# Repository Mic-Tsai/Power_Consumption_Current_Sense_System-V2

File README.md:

## Power Consumption | Current Sense System V2

Arduino based power consumption calculator. Print results as UART interface and OLED display, also have SD card to log data.

Maximum 8 differential channels, come out with 4x ADS1115 in one I2C bus. RGB OLED display (ST7789 130x160) results show as a real-time update also supports the SD card data log. 

** **Important** **

Before you log the power consumption results, the resistor value needs to be calculated by the multimeter. You can press the button to do the value change very quickly! 

After the data logging into the SD card, plot data into an image via a python script.
## 

Any question or need technical support:

* Contact me via mail (xbcke12345@gmail.com)
* If this project helping. Please generously support =)

##

## 

>### License Information
>>This product is open source! Both, our hardware and software are open source and licensed under the following:
>>#### Hardware
>>>All hardware is released under [Creative Commons Share-alike 4.0 International](http://creativecommons.org/licenses/by-sa/4.0/).
>>#### Software 
>>>All software is released under the MIT License [http://opensource.org/licenses/MIT](http://opensource.org/licenses/MIT).
>>#### Documentation
>>>The documentation on this page is released under [Creative Commons Share-alike 4.0 International](http://creativecommons.org/licenses/by-sa/4.0/).

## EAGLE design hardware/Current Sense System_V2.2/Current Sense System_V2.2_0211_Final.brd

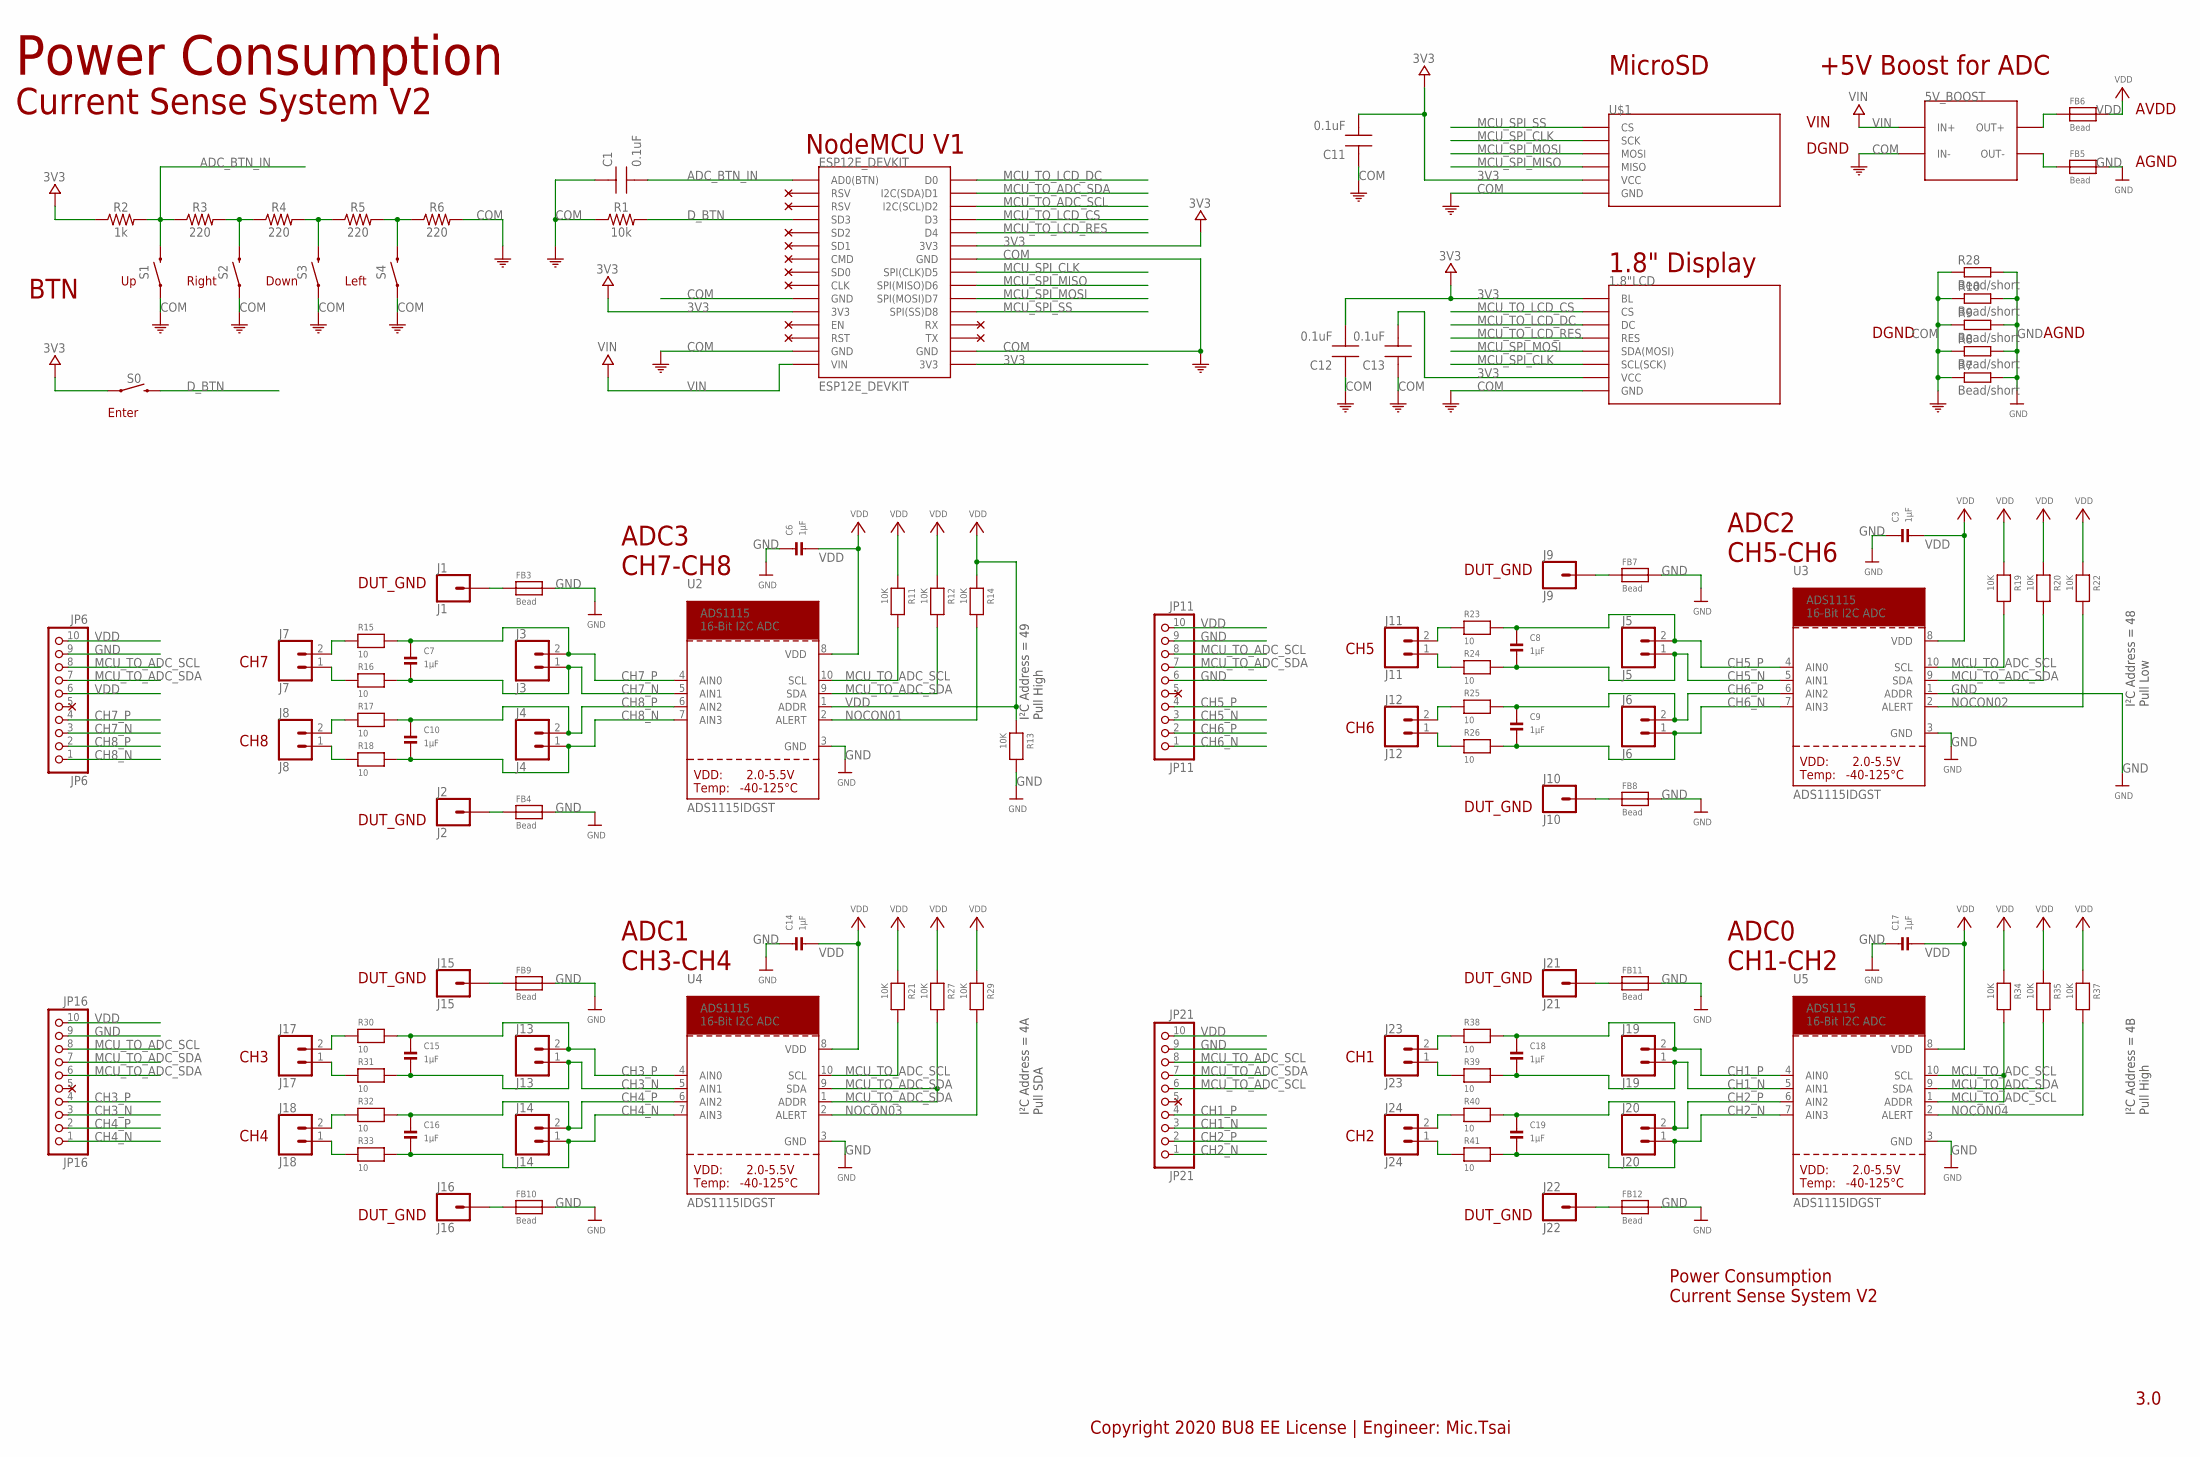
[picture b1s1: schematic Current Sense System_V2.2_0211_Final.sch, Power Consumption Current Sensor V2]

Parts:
1.8"LCD: 1.8"LCD"; 1.8"LCD
5V_BOOST: 5VBOOST"; 5VBOOST
C1, C11, C12, C13: 0.1uF; CAP0805-NP
C3, C6, C7, C8, C9, C10, C14, C15, C16, C17, C18, C19: 1µF; 0805
ESP12E_DEVKIT: ESP12E_DEVKIT
FB3, FB4, FB5, FB6, FB7, FB8, FB9, FB10, FB11, FB12: Bead; 0805
J1: J1; 1X01
J2: J2; 1X01
J3: J3; 1X02
J4: J4; 1X02
J5: J5; 1X02
J6: J6; 1X02
J7: J7; 1X02
J8: J8; 1X02
J9: J9; 1X01
J10: J10; 1X01
J11: J11; 1X02
J12: J12; 1X02
J13: J13; 1X02
J14: J14; 1X02
J15: J15; 1X01
J16: J16; 1X01
J17: J17; 1X02
J18: J18; 1X02
J19: J19; 1X02
J20: J20; 1X02
J21: J21; 1X01
J22: J22; 1X01
J23: J23; 1X02
J24: J24; 1X02
JP6: JP6; 1X10_ROUND70
JP11: JP11; 1X10_ROUND70
JP16: JP16; 1X10_ROUND70
JP21: JP21; 1X10_ROUND70
R1: 10k; 0805
R2: 1k; 0805
R3, R4, R5, R6: 220; 0805
R7, R8, R9, R10, R28: Bead/short; R0603
R11, R12, R13, R14, R19, R20, R21, R22, R27, R29, R34, R35, R37: 10K; 0805
R15, R16, R17, R18, R23, R24, R25, R26, R30, R31, R32, R33, R38, R39, R40, R41: 10; 0805
S0, S1, S2, S3, S4: MOMENTARY-SWITCH-SPST-PTH-6.0MM; TACTILE_SWITCH_PTH_6.0MM
U2, U3, U4, U5: ADS1115IDGST; MSOP10
U$1: MICROSD"; MICROSD

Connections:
3V3: 1.8"LCD.BL, 1.8"LCD.VCC(3V3) (VCC), C11.2, C12.2, C13.2, ESP12E_DEVKIT.3V3@0 (3V3), ESP12E_DEVKIT.3V3@1 (3V3), ESP12E_DEVKIT.3V3@2 (3V3), R2.1, S0.1, U$1.VCC(5V) (VCC)
ADC_BTN_IN: C1.2, ESP12E_DEVKIT.AD0 (AD0(BTN)), R2.2, R3.1, S1.3 (2)
CH1_N: C18.2, J19.1, JP21.3, R39.2, U5.5 (AIN1)
CH1_P: C18.1, J19.2, JP21.4, R38.2, U5.4 (AIN0)
CH2_N: C19.2, J20.1, JP21.1, R41.2, U5.7 (AIN3)
CH2_P: C19.1, J20.2, JP21.2, R40.2, U5.6 (AIN2)
CH3_N: C15.2, J13.1, JP16.3, R31.2, U4.5 (AIN1)
CH3_P: C15.1, J13.2, JP16.4, R30.2, U4.4 (AIN0)
CH4_N: C16.2, J14.1, JP16.1, R33.2, U4.7 (AIN3)
CH4_P: C16.1, J14.2, JP16.2, R32.2, U4.6 (AIN2)
CH5_N: C8.2, J5.1, JP11.3, R24.2, U3.5 (AIN1)
CH5_P: C8.1, J5.2, JP11.4, R23.2, U3.4 (AIN0)
CH6_N: C9.2, J6.1, JP11.1, R26.2, U3.7 (AIN3)
CH6_P: C9.1, J6.2, JP11.2, R25.2, U3.6 (AIN2)
CH7_N: C7.2, J3.1, JP6.3, R16.2, U2.5 (AIN1)
CH7_P: C7.1, J3.2, JP6.4, R15.2, U2.4 (AIN0)
CH8_N: C10.2, J4.1, JP6.1, R18.2, U2.7 (AIN3)
CH8_P: C10.1, J4.2, JP6.2, R17.2, U2.6 (AIN2)
COM: 1.8"LCD.GND, 5V_BOOST.IN-, C1.1, C11.1, C12.1, C13.1, ESP12E_DEVKIT.GND@0 (GND), ESP12E_DEVKIT.GND@1 (GND), ESP12E_DEVKIT.GND@2 (GND), ESP12E_DEVKIT.GND@3 (GND), R1.1, R6.2, R7.1, R8.1, R9.1, R10.1, R28.1, S1.1, S2.1, S3.1, S4.1, U$1.GND
D_BTN: ESP12E_DEVKIT.SD3, R1.2, S0.3 (2)
GND: C3.1, C6.1, C14.1, C17.1, FB3.2, FB4.2, FB5.2, FB7.2, FB8.2, FB9.2, FB10.2, FB11.2, FB12.2, JP6.9, JP11.6, JP11.9, JP16.9, JP21.9, R7.2, R8.2, R9.2, R10.2, R13.2, R28.2, U2.3 (GND), U3.1 (ADDR), U3.3 (GND), U4.3 (GND), U5.3 (GND)
MCU_SPI_CLK: 1.8"LCD.SCL(SCK), ESP12E_DEVKIT.D5 (SPI(CLK)D5), U$1.SCK
MCU_SPI_MISO: ESP12E_DEVKIT.D6 (SPI(MISO)D6), U$1.MISO
MCU_SPI_MOSI: 1.8"LCD.SDA(MOSI), ESP12E_DEVKIT.D7 (SPI(MOSI)D7), U$1.MOSI
MCU_SPI_SS: ESP12E_DEVKIT.D8 (SPI(SS)D8), U$1.CS
MCU_TO_ADC_SCL: ESP12E_DEVKIT.D2 (I2C(SCL)D2), JP6.8, JP11.8, JP16.8, JP21.6, JP21.8, R11.2, R19.2, R21.2, R34.2, U2.10 (SCL), U3.10 (SCL), U4.10 (SCL), U5.1 (ADDR), U5.10 (SCL)
MCU_TO_ADC_SDA: ESP12E_DEVKIT.D1 (I2C(SDA)D1), JP6.7, JP11.7, JP16.6, JP16.7, JP21.7, R12.2, R20.2, R27.2, R35.2, U2.9 (SDA), U3.9 (SDA), U4.1 (ADDR), U4.9 (SDA), U5.9 (SDA)
MCU_TO_LCD_CS: 1.8"LCD.CS, ESP12E_DEVKIT.D3
MCU_TO_LCD_DC: 1.8"LCD.DC, ESP12E_DEVKIT.D0
MCU_TO_LCD_RES: 1.8"LCD.RES, ESP12E_DEVKIT.D4
unnamed: FB3.1, J1.1
unnamed: FB4.1, J2.1
unnamed: J7.2, R15.1
unnamed: J7.1, R16.1
unnamed: J8.2, R17.1
unnamed: J8.1, R18.1
unnamed: 5V_BOOST.OUT-, FB5.1
unnamed: 5V_BOOST.OUT+, FB6.1
unnamed: FB7.1, J9.1
unnamed: FB8.1, J10.1
unnamed: J11.2, R23.1
unnamed: J11.1, R24.1
unnamed: J12.2, R25.1
unnamed: J12.1, R26.1
unnamed: FB9.1, J15.1
unnamed: R3.2, R4.1, S2.3 (2)
unnamed: R4.2, R5.1, S3.3 (2)
unnamed: R5.2, R6.1, S4.3 (2)
unnamed: FB10.1, J16.1
unnamed: J17.2, R30.1
unnamed: J17.1, R31.1
unnamed: J18.2, R32.1
unnamed: J18.1, R33.1
unnamed: FB11.1, J21.1
unnamed: FB12.1, J22.1
unnamed: J23.2, R38.1
unnamed: J23.1, R39.1
unnamed: J24.2, R40.1
unnamed: J24.1, R41.1
NOCON01: R14.2, U2.2 (ALERT)
NOCON02: R22.2, U3.2 (ALERT)
NOCON03: R29.2, U4.2 (ALERT)
NOCON04: R37.2, U5.2 (ALERT)
VDD: C3.2, C6.2, C14.2, C17.2, FB6.2, JP6.6, JP6.10, JP11.10, JP16.10, JP21.10, R11.1, R12.1, R13.1, R14.1, R19.1, R20.1, R21.1, R22.1, R27.1, R29.1, R34.1, R35.1, R37.1, U2.1 (ADDR), U2.8 (VDD), U3.8 (VDD), U4.8 (VDD), U5.8 (VDD)
VIN: 5V_BOOST.IN+, ESP12E_DEVKIT.VIN

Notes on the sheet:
Power Consumption
3.0
NodeMCU V1
+5V Boost for ADC
Power Consumption Current Sense System V2
Current Sense System V2
BTN
Right
Down
Left
Enter
1.8" Display
MicroSD
I²C Address = 49 Pull High
ADC3 CH7-CH8
ADS1115 16-Bit I2C ADC
CH7
CH8
DUT_GND
I²C Address = 48 Pull Low
ADC2 CH5-CH6
CH5
CH6
I²C Address = 4A Pull SDA
ADC1 CH3-CH4
CH3
CH4
I²C Address = 4B Pull High
ADC0 CH1-CH2
CH1
CH2
AVDD
AGND
VIN
DGND
Copyright 2020 BU8 EE License | Engineer: Mic.Tsai

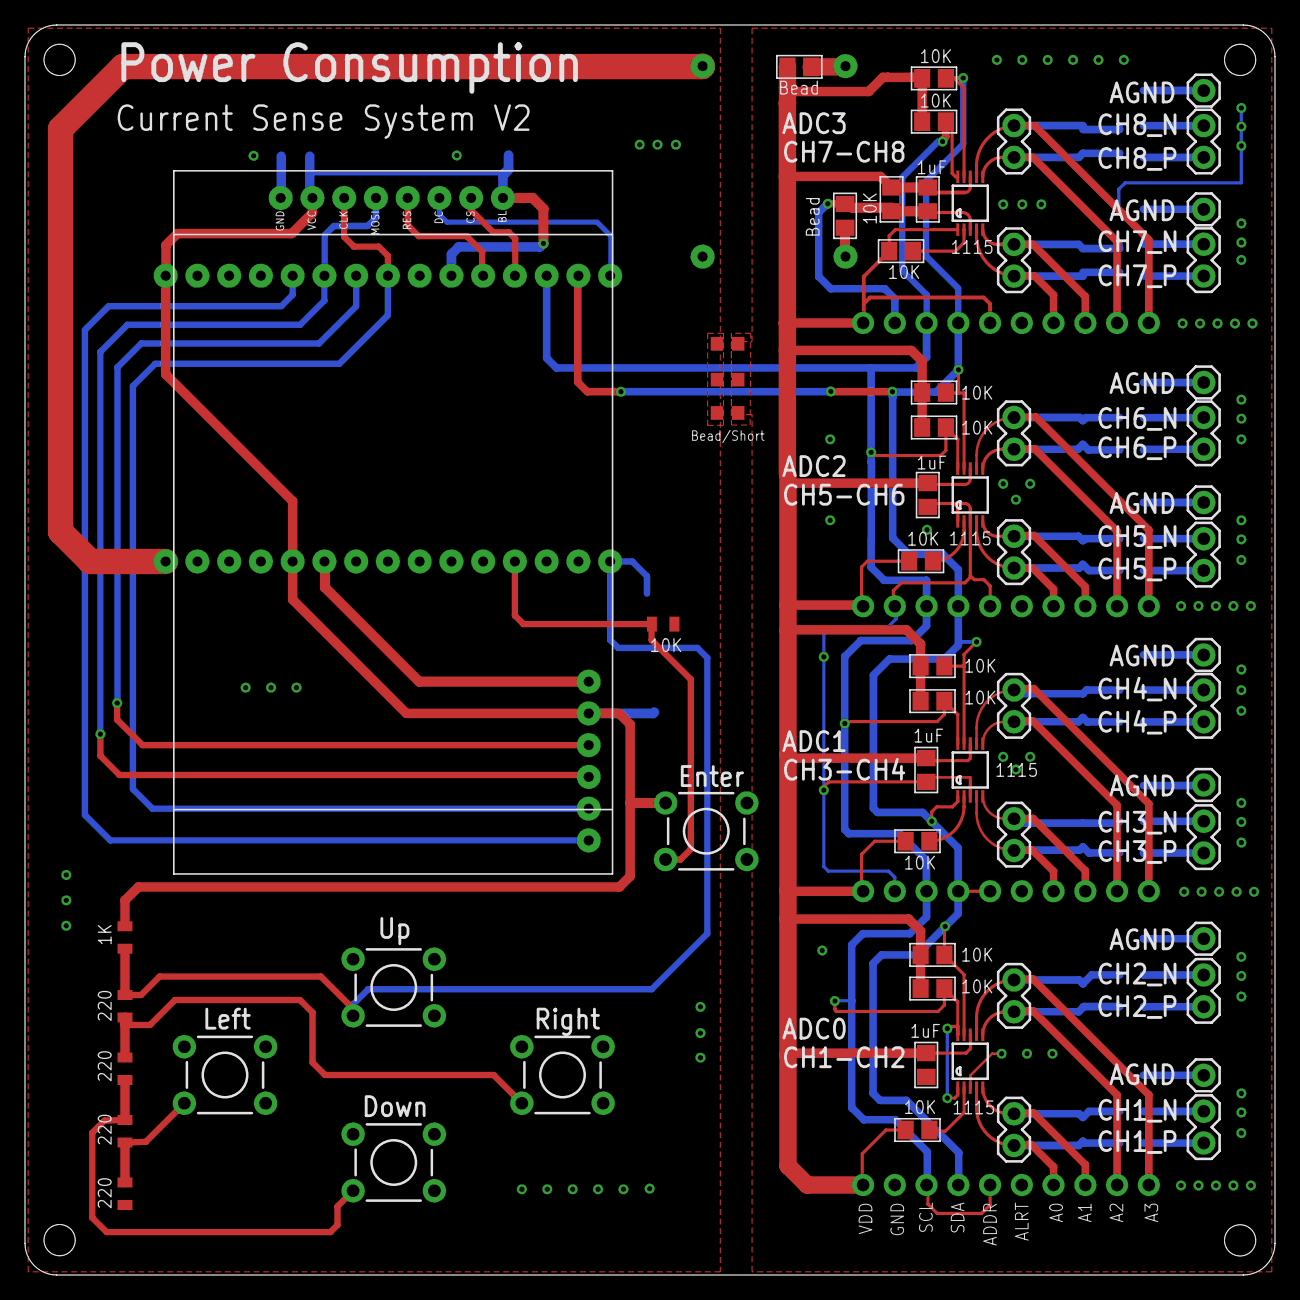
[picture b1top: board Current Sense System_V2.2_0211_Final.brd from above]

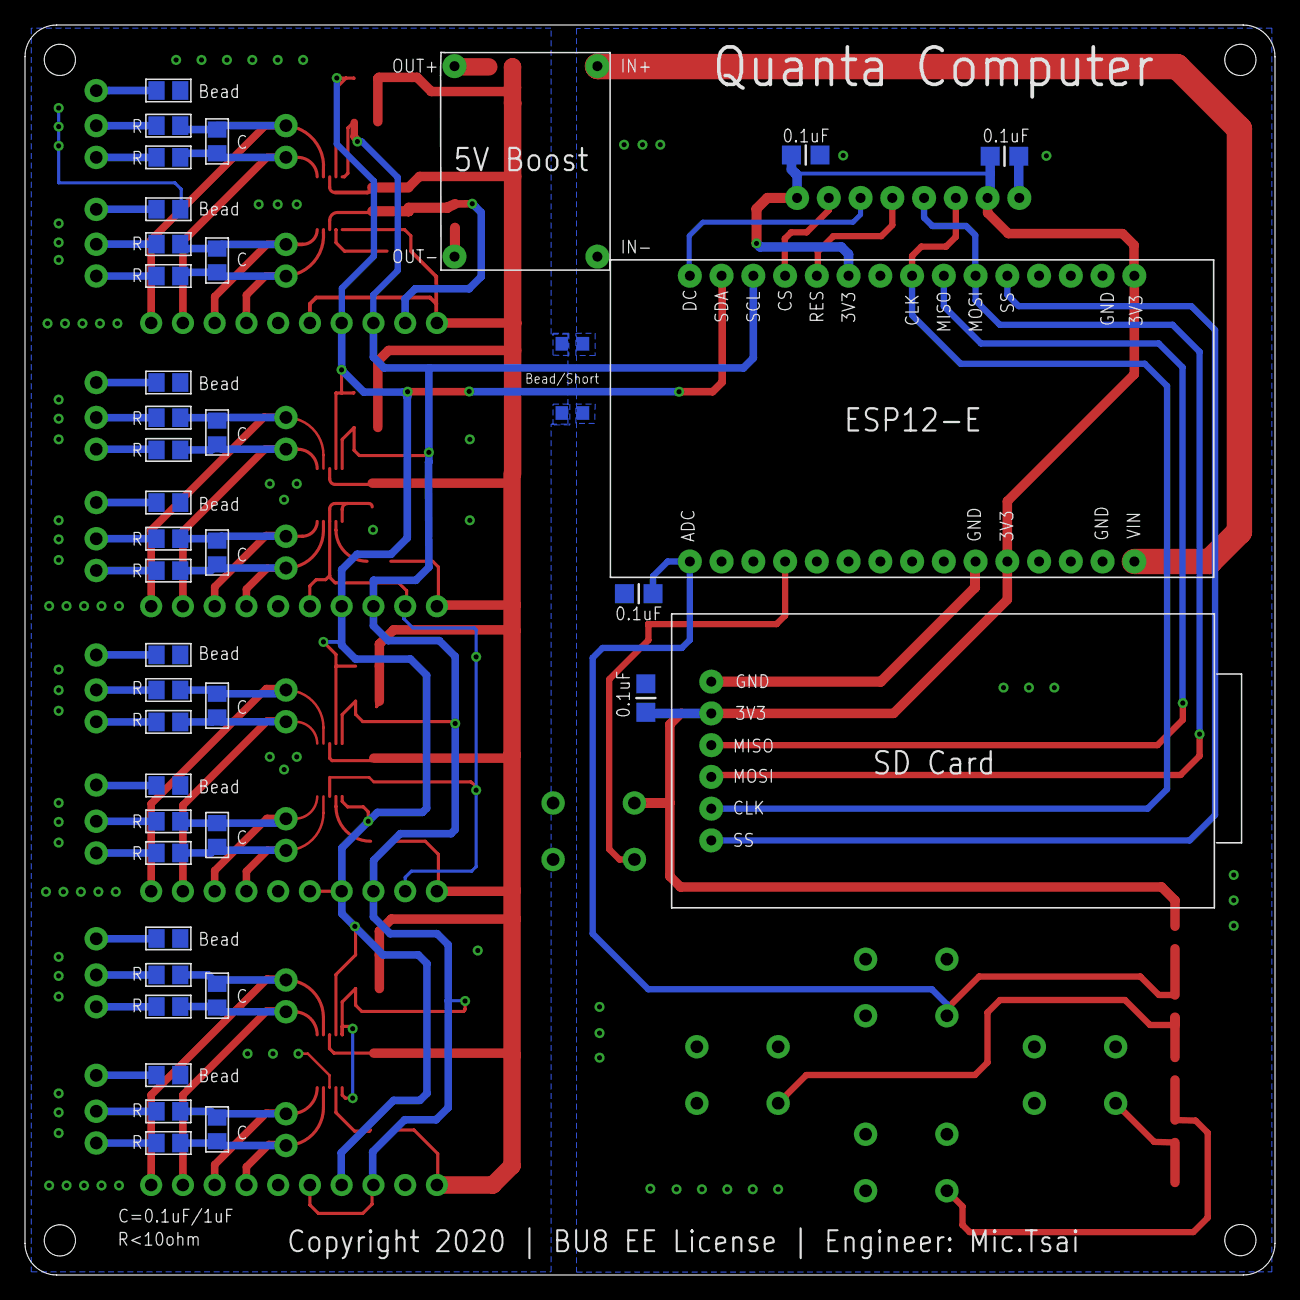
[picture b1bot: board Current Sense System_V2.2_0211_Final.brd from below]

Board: 2 copper layers, 100.0 x 100.0 mm, 107 parts (41 on the bottom side), 65 nets.

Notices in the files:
parts and their libraries:
SparkFun-Resistors: Licensing: Creative Commons ShareAlike 4.0 International - https://creativecommons.org/licenses/by-sa/4.0
